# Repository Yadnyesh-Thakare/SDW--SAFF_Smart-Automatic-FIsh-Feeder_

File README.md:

# SDW--SAFF_Smart-Automatic-FIsh-Feeder_
This automated smart fish feeder uses an ESP8266 microcontroller paired with a Real-Time Clock (RTC) module to precisely schedule feeding times and portion sizes with servo.
By using the ESP8266's built-in Wi-Fi, the system hosts a secure, encrypted local web server, allowing you to control all feeding schedules and light settings directly from your phone or computer.
It also indicate low food in storage container.
For sudden power loss we also have added battery to keep the system working during power loss. 

. For 3d Design refer this -> [https://a360.co/4jwVF6T]

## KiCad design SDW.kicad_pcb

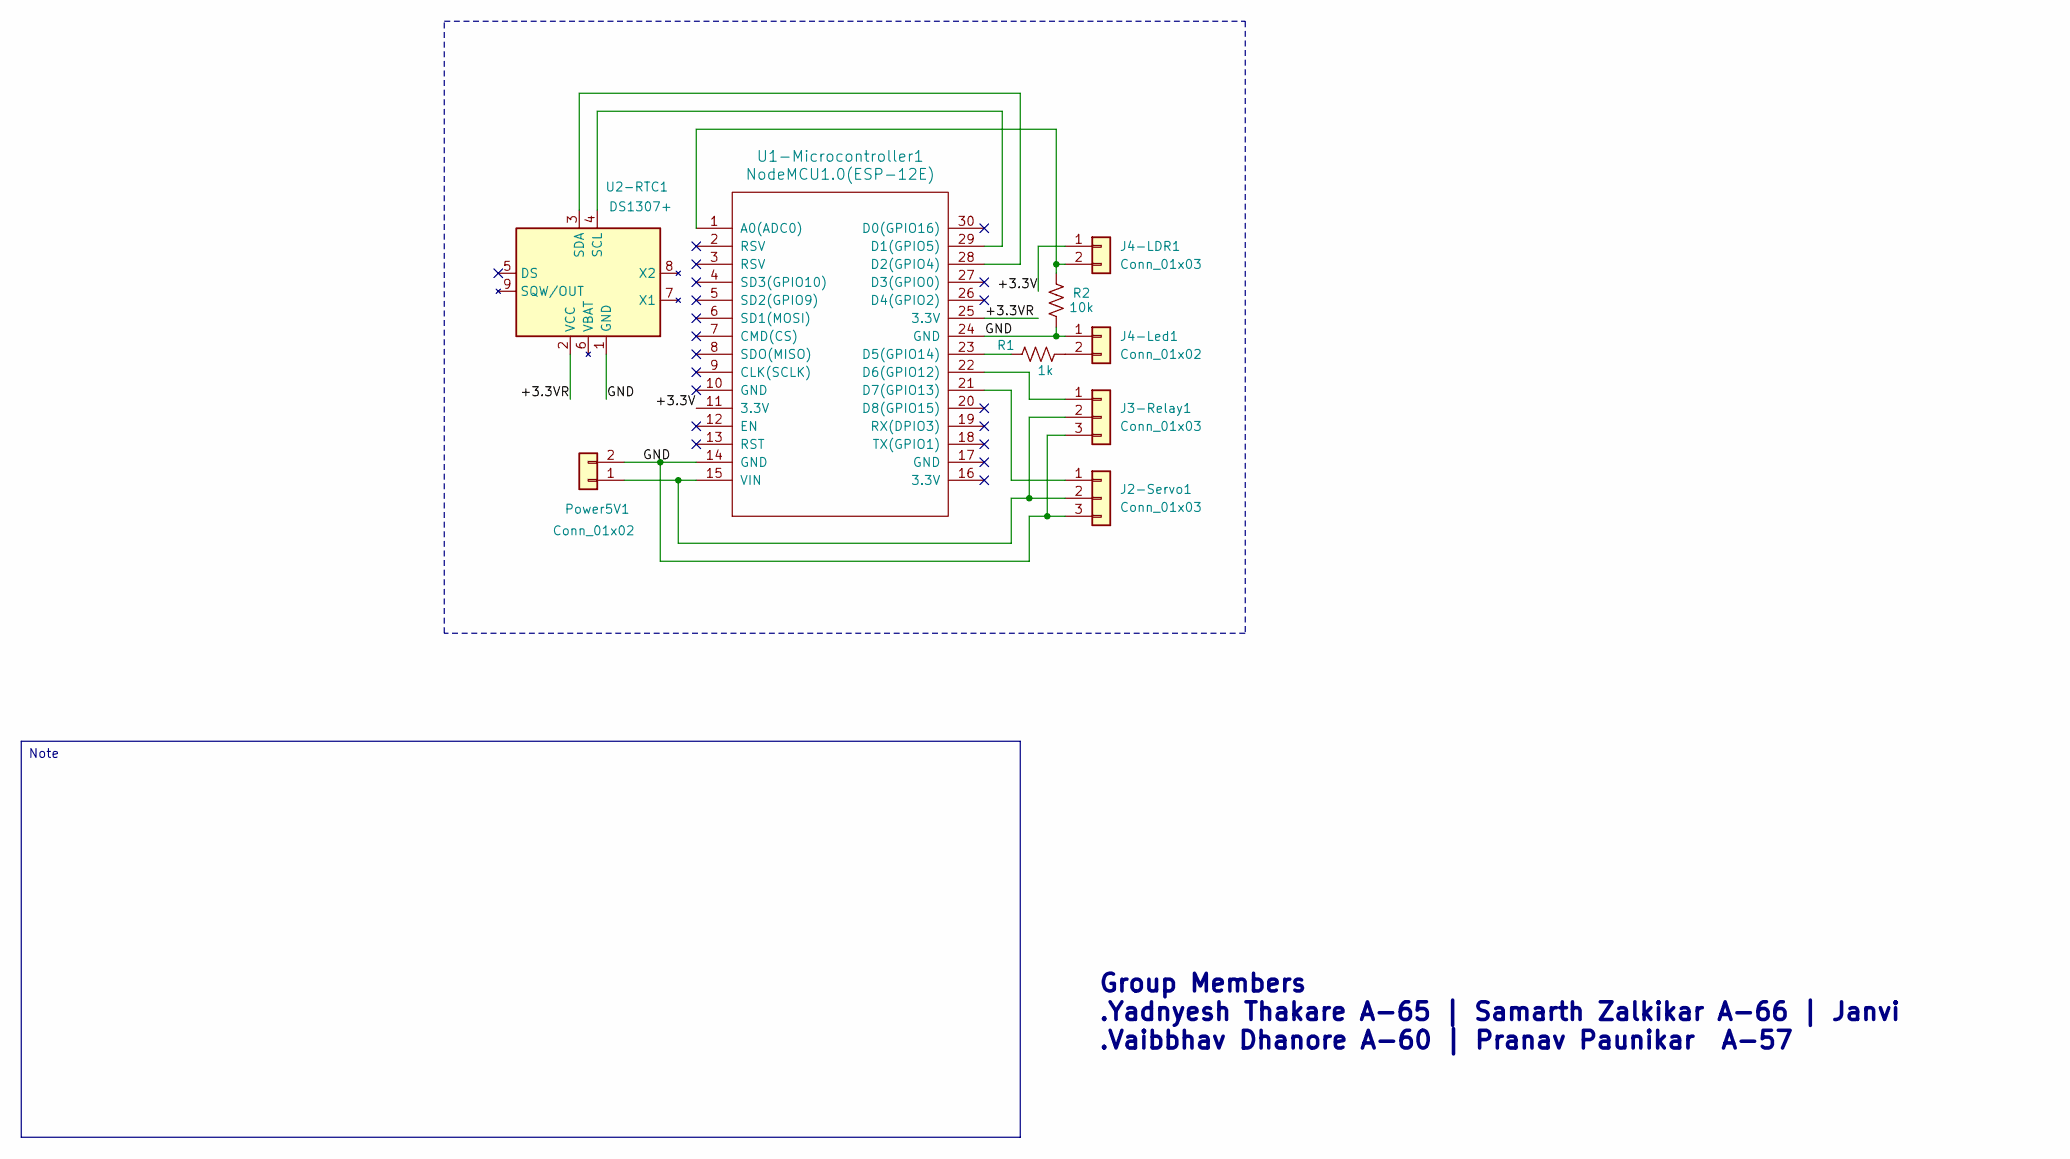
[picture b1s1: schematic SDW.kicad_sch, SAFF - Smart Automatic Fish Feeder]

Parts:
J2-Servo1, J3-Relay1: Conn_01x03; PinHeader_1x03_P2.54mm_Vertical
J4-LDR1: Conn_01x03; PinHeader_1x02_P2.54mm_Vertical
J4-Led1: Conn_01x02; PinHeader_1x02_P2.54mm_Vertical
Power5V1: Conn_01x02; PinHeader_1x02_P2.54mm_Vertical
R1: 1k; R_Axial_DIN0204_L3.6mm_D1.6mm_P5.08mm_Horizontal
R2: 10k; R_Axial_DIN0204_L3.6mm_D1.6mm_P5.08mm_Horizontal
U1-Microcontroller1: NodeMCU1.0(ESP-12E); NodeMCU1.0(12-E)
U2-RTC1: DS1307+; PinHeader_1x05_P2.54mm_Vertical

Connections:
/+3.3V: J4-LDR1.1, U1-Microcontroller1.11 (3.3V)
/+3.3VR: U1-Microcontroller1.25 (3.3V), U2-RTC1.2 (VCC)
/GND: J2-Servo1.3, J3-Relay1.3, J4-Led1.1, Power5V1.2, R2.2, U1-Microcontroller1.14 (GND), U1-Microcontroller1.24 (GND), U2-RTC1.1 (GND)
unnamed: J2-Servo1.1, U1-Microcontroller1.21 (D7(GPIO13))
unnamed: J2-Servo1.2, J3-Relay1.2, Power5V1.1, U1-Microcontroller1.15 (VIN)
unnamed: J3-Relay1.1, U1-Microcontroller1.22 (D6(GPIO12))
unnamed: J4-LDR1.2, R2.1, U1-Microcontroller1.1 (A0(ADC0))
unnamed: J4-Led1.2, R1.1
unnamed: U1-Microcontroller1.29 (D1(GPIO5)), U2-RTC1.4 (SCL)
unnamed: U1-Microcontroller1.28 (D2(GPIO4)), U2-RTC1.3 (SDA)
unnamed: R1.2, U1-Microcontroller1.23 (D5(GPIO14))

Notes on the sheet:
Group Members .Yadnyesh Thakare A-65 | Samarth Zalkikar A-66 | Janvi .Vaibbhav Dhanore A-60 | Pranav Paunikar A-57
Note

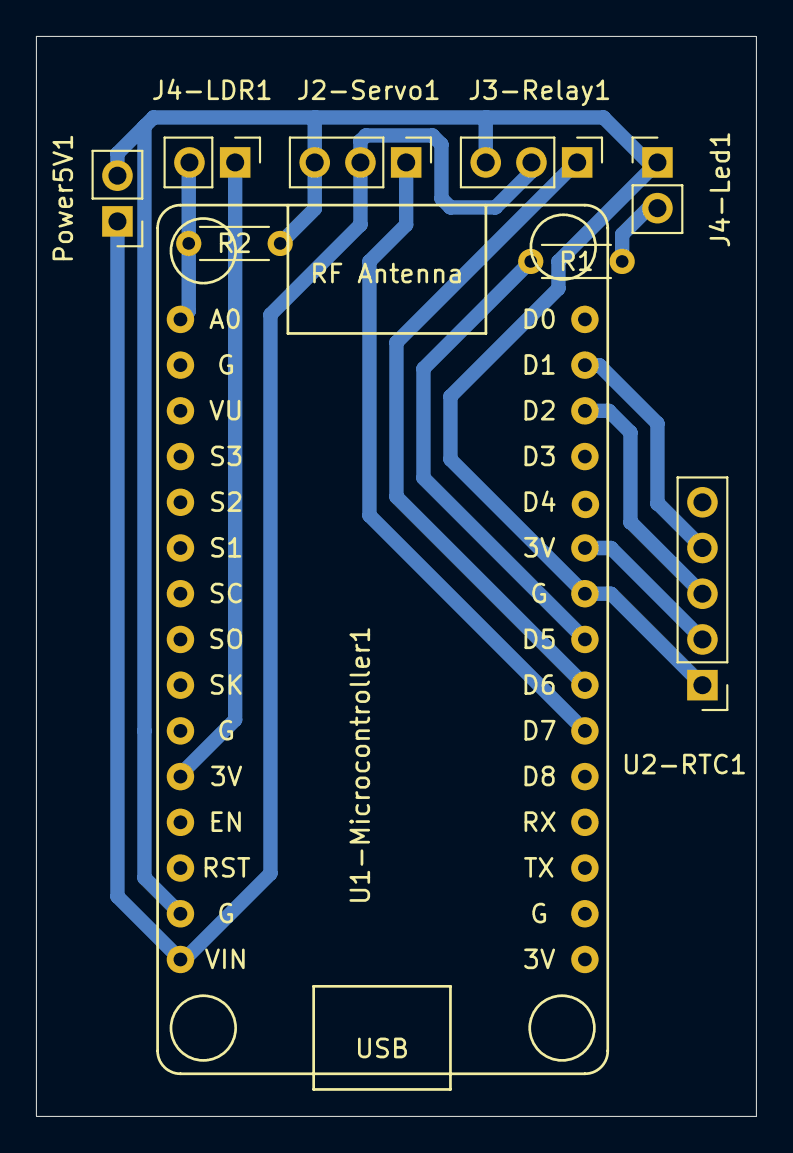
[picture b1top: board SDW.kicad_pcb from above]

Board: 2 copper layers, 40.0 x 60.0 mm, 9 parts (0 on the bottom side), 11 nets.
